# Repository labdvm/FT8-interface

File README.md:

# FT8-interface
FT8 and others digi-modes interface from computer to radio
The radio from computer is galvanic separated !

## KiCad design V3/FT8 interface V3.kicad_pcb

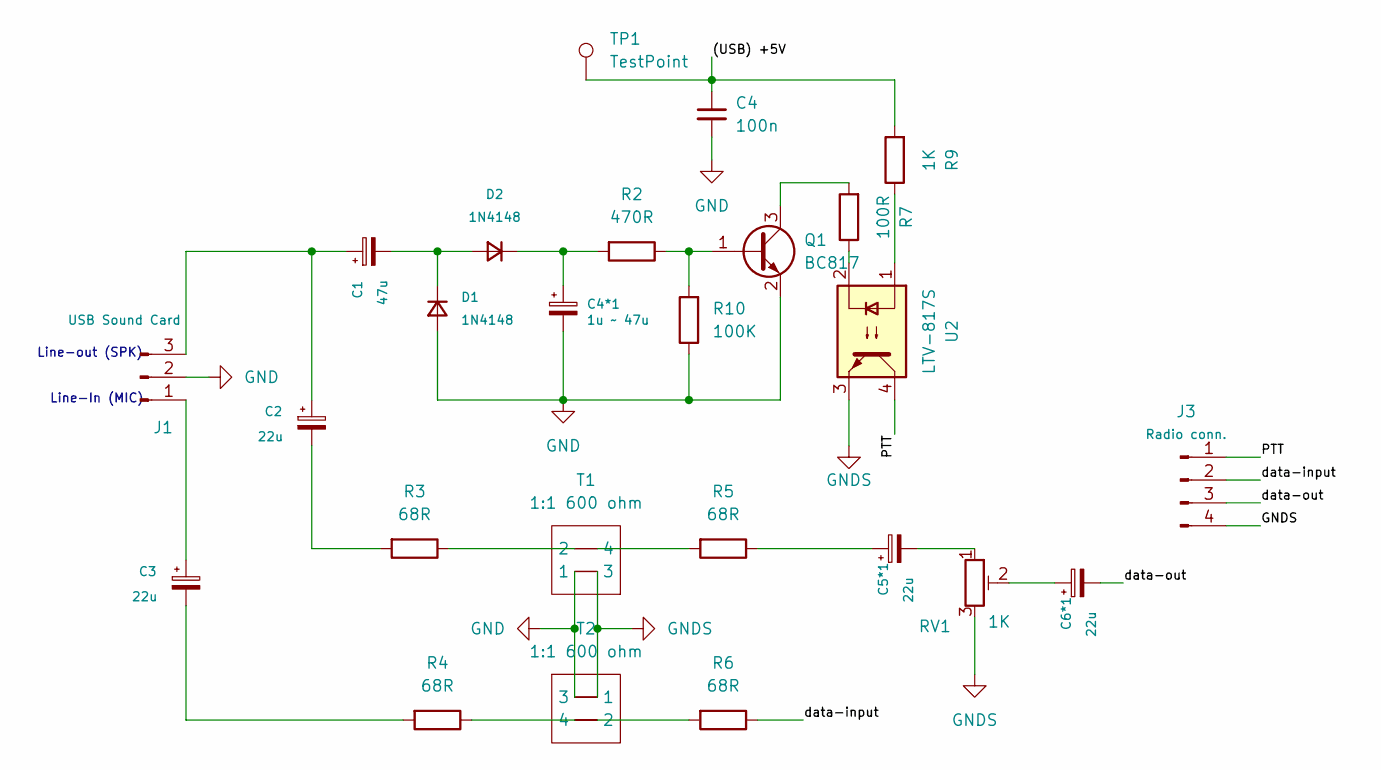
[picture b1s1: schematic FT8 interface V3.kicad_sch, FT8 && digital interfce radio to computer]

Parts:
C1: 47u; CP_EIA-3216-10_Kemet-I
C2, C3, C5*1, C6*1: 22u; CP_EIA-3216-10_Kemet-I
C4: 100n; C_0603_1608Metric
C4*1: 1u ~ 47u; CP_EIA-3216-10_Kemet-I
D1, D2: 1N4148; D_SOD-523
J1: USB Sound Card; PinHeader_1x03_P2.54mm_Horizontal
J3: Radio conn.; PinHeader_1x04_P2.54mm_Vertical
Q1: BC817; SOT-23
R2: 470R; R_0603_1608Metric
R3, R4, R5, R6: 68R; R_0603_1608Metric
R7: 100R; R_0603_1608Metric
R9: 1K; R_0603_1608Metric
R10: 100K; R_0603_1608Metric
RV1: 1K; Potentiometer_Bourns_3314J_Vertical
T1, T2: 1:1 600 ohm; Transformer_ED8_4-Lead_10.5x8mm_P5mm
TP1: TestPoint; TestPoint_Loop_D2.50mm_Drill1.0mm
U2: LTV-817S; SMDIP-4_W9.53mm

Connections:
/(USB) +5V: C4.1, R9.2, TP1.1; also elsewhere on the board
/PTT: J3.1, U2.4
/data-input: J3.2, R6.1
/data-out: C6*1.2, J3.3
GND: C4.2, C4*1.2, D1.2 (A), J1.2, Q1.2 (E), R10.1, T1.3, T2.1
GNDS: J3.4, RV1.3, T1.1, T2.3, U2.3
unnamed: C2.2, R3.2
unnamed: C3.2, R4.2
unnamed: C5*1.1, R5.1
unnamed: C5*1.2, RV1.1
unnamed: C6*1.1, RV1.2
unnamed: C1.2, D1.1 (K), D2.2 (A)
unnamed: C4*1.1, D2.1 (K), R2.2
unnamed: C3.1, J1.1
unnamed: C1.1, C2.1, J1.3
unnamed: Q1.1 (B), R2.1, R10.2
unnamed: Q1.3 (C), R7.2
unnamed: R3.1, T1.4
unnamed: R4.1, T2.2
unnamed: R5.2, T1.2
unnamed: R6.2, T2.4
unnamed: R7.1, U2.2
unnamed: R9.1, U2.1

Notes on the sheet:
Line-out (SPK)
Line-In (MIC)

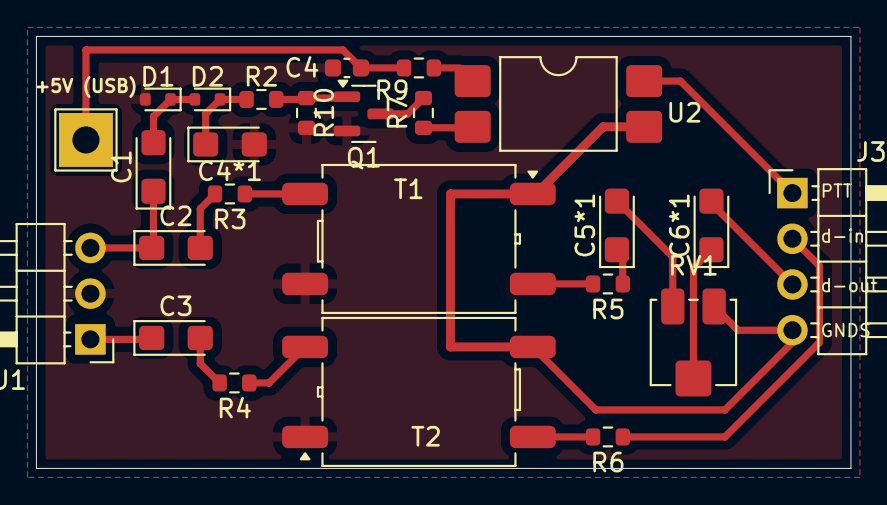
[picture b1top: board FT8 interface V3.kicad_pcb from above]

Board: 2 copper layers, 45.2 x 24.0 mm, 25 parts (0 on the bottom side), 23 nets.

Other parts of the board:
+5V (USB): TestPoint; TestPoint_THTPad_3.0x3.0mm_Drill1.5mm

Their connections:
/(USB) +5V: +5V (USB).1; also elsewhere on the board

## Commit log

2026-02-01 Fix grammatical error in README description
